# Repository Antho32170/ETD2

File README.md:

# SESAME
Projet ETD18 BALMA

The SESAME project is a DC-DC converter which can be pluged from either side.

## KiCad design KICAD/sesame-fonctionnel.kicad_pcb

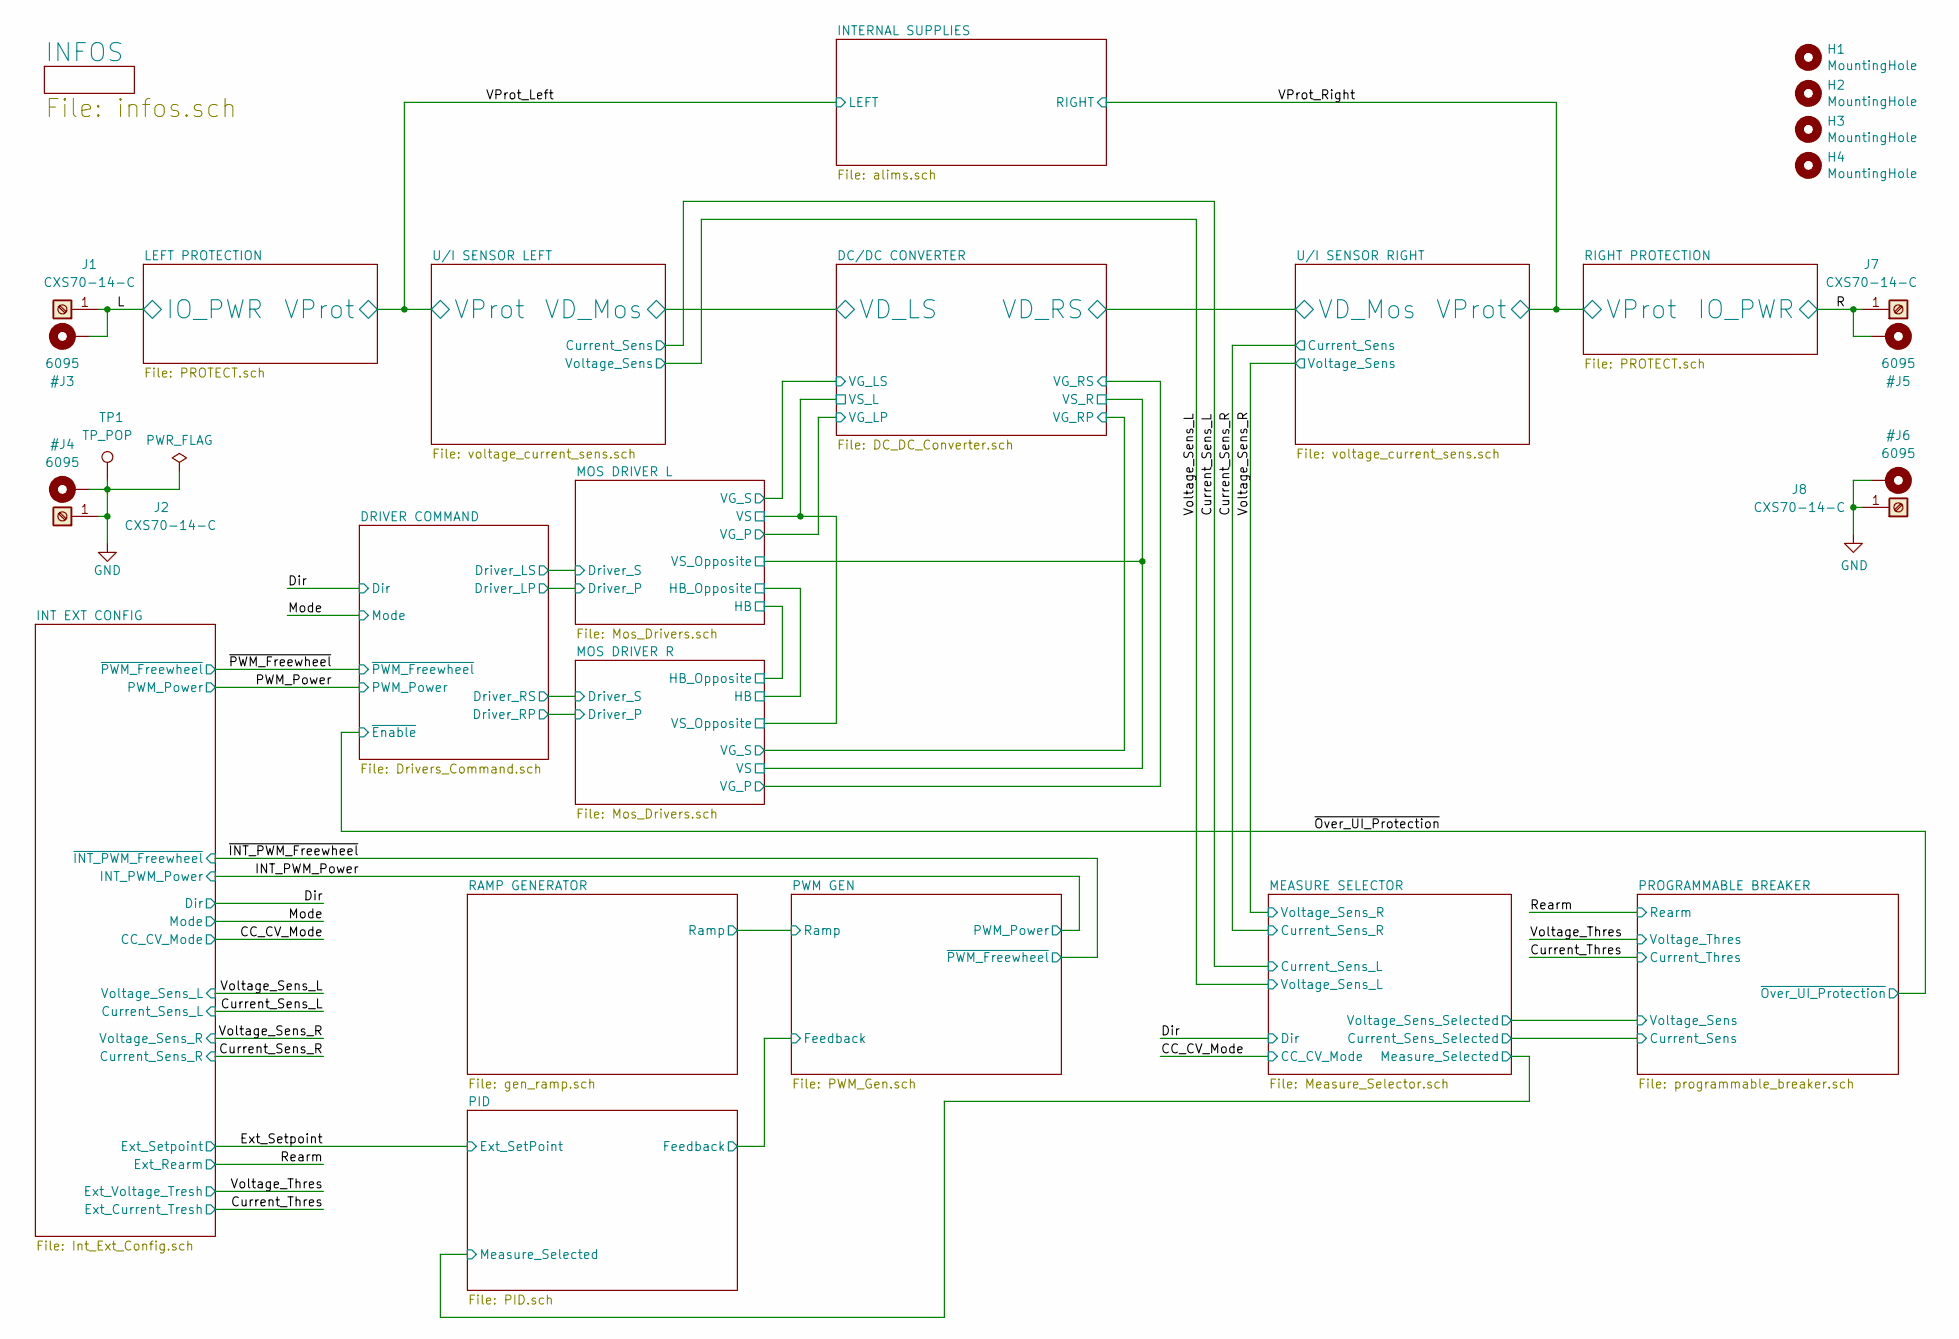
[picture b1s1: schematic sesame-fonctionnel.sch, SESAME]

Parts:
H1, H2, H3, H4: MountingHole; MountingHole_3.2mm_M3
J1, J2, J7, J8: CXS70-14-C
TP1: TP_POP; TestPoint_Loop_D1.80mm_Drill1.0mm_Beaded

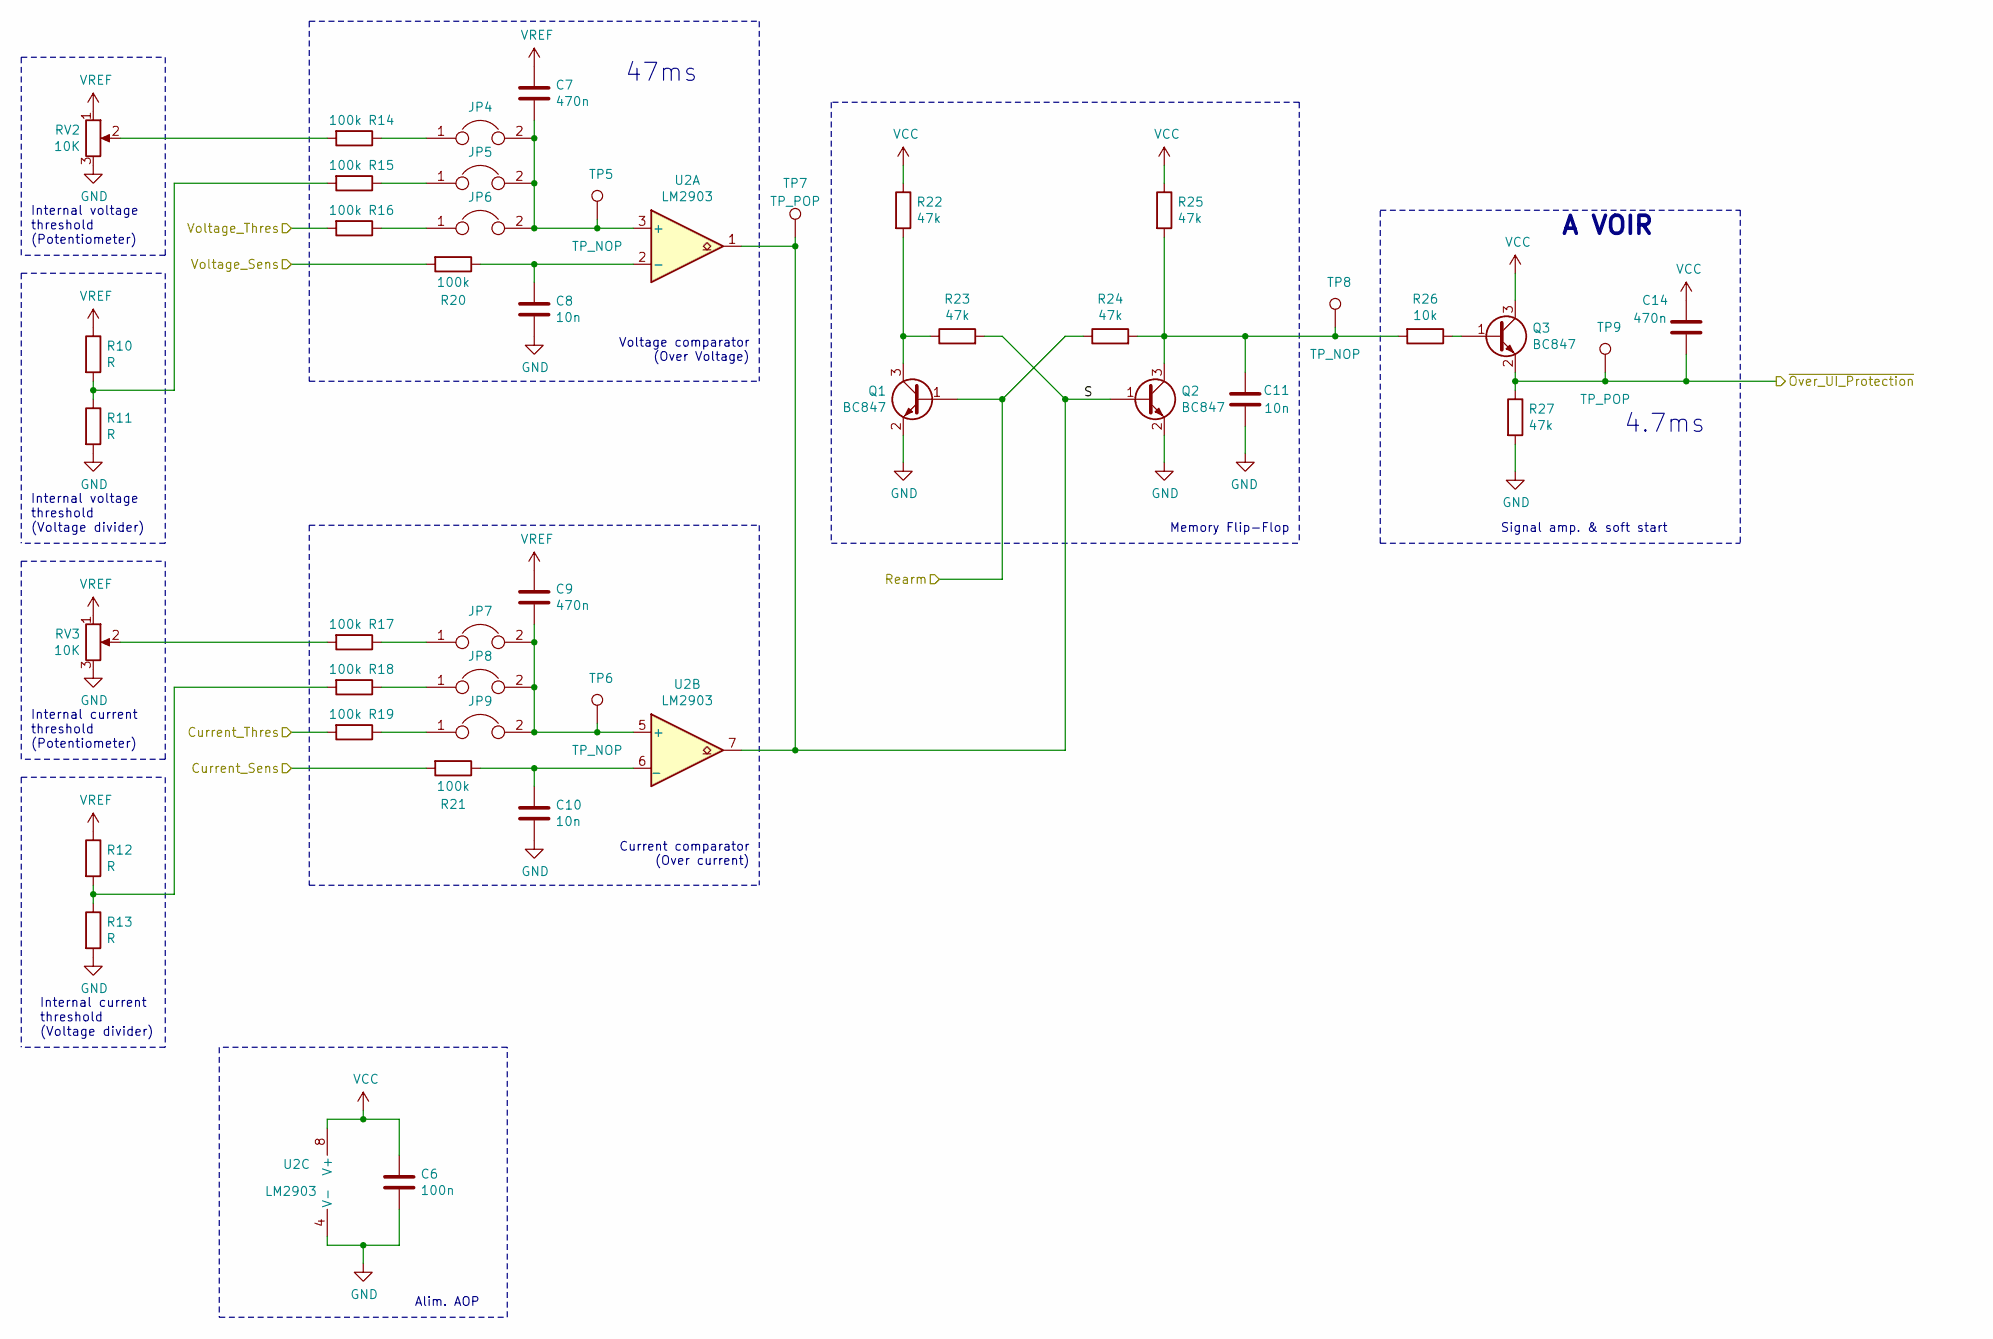
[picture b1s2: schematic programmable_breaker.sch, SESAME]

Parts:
C6: 100n; C_0805_2012Metric_Pad1.18x1.45mm_HandSolder
C7, C9, C14: 470n; C_0805_2012Metric_Pad1.18x1.45mm_HandSolder
C8, C10, C11: 10n; C_0805_2012Metric_Pad1.18x1.45mm_HandSolder
JP4, JP5, JP6, JP7, JP8, JP9: Jumper; PinHeader_1x02_P2.54mm_Vertical
Q1, Q2, Q3: BC847; SOT-23
R10, R11, R12, R13: R; R_0805_2012Metric_Pad1.20x1.40mm_HandSolder
R14, R15, R16, R17, R18, R19, R20, R21: 100k; R_0805_2012Metric_Pad1.20x1.40mm_HandSolder
R22, R23, R24, R25, R27: 47k; R_0805_2012Metric_Pad1.20x1.40mm_HandSolder
R26: 10k; R_0805_2012Metric_Pad1.20x1.40mm_HandSolder
RV2, RV3: 10K; Potentiometer_Bourns_3214W_Vertical
TP5, TP6, TP8: TP_NOP; TestPoint_THTPad_D2.0mm_Drill1.0mm
TP7, TP9: TP_POP; TestPoint_Loop_D1.80mm_Drill1.0mm_Beaded
U2: LM2903; SO-8_5.3x6.2mm_P1.27mm

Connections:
/Current_Thres: R19.2; also elsewhere on the board
/PROGRAMMABLE BREAKER/Current_Sens: R21.2; also elsewhere on the board
/PROGRAMMABLE BREAKER/S: Q2.1 (B), R23.2, TP7.1, U2.1, U2.7
/PROGRAMMABLE BREAKER/Voltage_Sens: R20.2; also elsewhere on the board
/Rearm: Q1.1 (B), R24.1; also elsewhere on the board
/Voltage_Thres: R16.2; also elsewhere on the board
/~Over_UI_Protection: C14.2, Q3.2 (E), R27.1, TP9.1; also elsewhere on the board
unnamed: C7.2, JP4.2, JP5.2, JP6.2, TP5.1, U2.3 (+)
unnamed: C8.1, R20.1, U2.2 (-)
unnamed: C9.2, JP7.2, JP8.2, JP9.2, TP6.1, U2.5 (+)
unnamed: C10.1, R21.1, U2.6 (_)
unnamed: C11.1, Q2.3 (C), R24.2, R25.2, R26.2, TP8.1
unnamed: JP4.1, R14.1
unnamed: JP5.1, R15.1
unnamed: JP6.1, R16.1
unnamed: JP7.1, R17.1
unnamed: JP8.1, R18.1
unnamed: JP9.1, R19.1
unnamed: Q1.3 (C), R22.2, R23.1
unnamed: Q3.1 (B), R26.1
unnamed: R10.2, R11.1, R15.2
unnamed: R12.2, R13.1, R18.2
unnamed: R14.2, RV2.2
unnamed: R17.2, RV3.2
VCC: C6.1, C14.1, Q3.3 (C), R22.1, R25.1, U2.8 (V+); also elsewhere on the board
VREF: C7.1, C9.1, R10.1, R12.1, RV2.1, RV3.1; also elsewhere on the board

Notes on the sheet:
Voltage comparator (Over Voltage)
Memory Flip-Flop
Alim. AOP
Signal amp. & soft start
Internal voltage threshold (Potentiometer)
Internal voltage threshold (Voltage divider)
Current comparator (Over current)
Internal current threshold (Voltage divider)
Internal current threshold (Potentiometer)
4.7ms
47ms
A VOIR

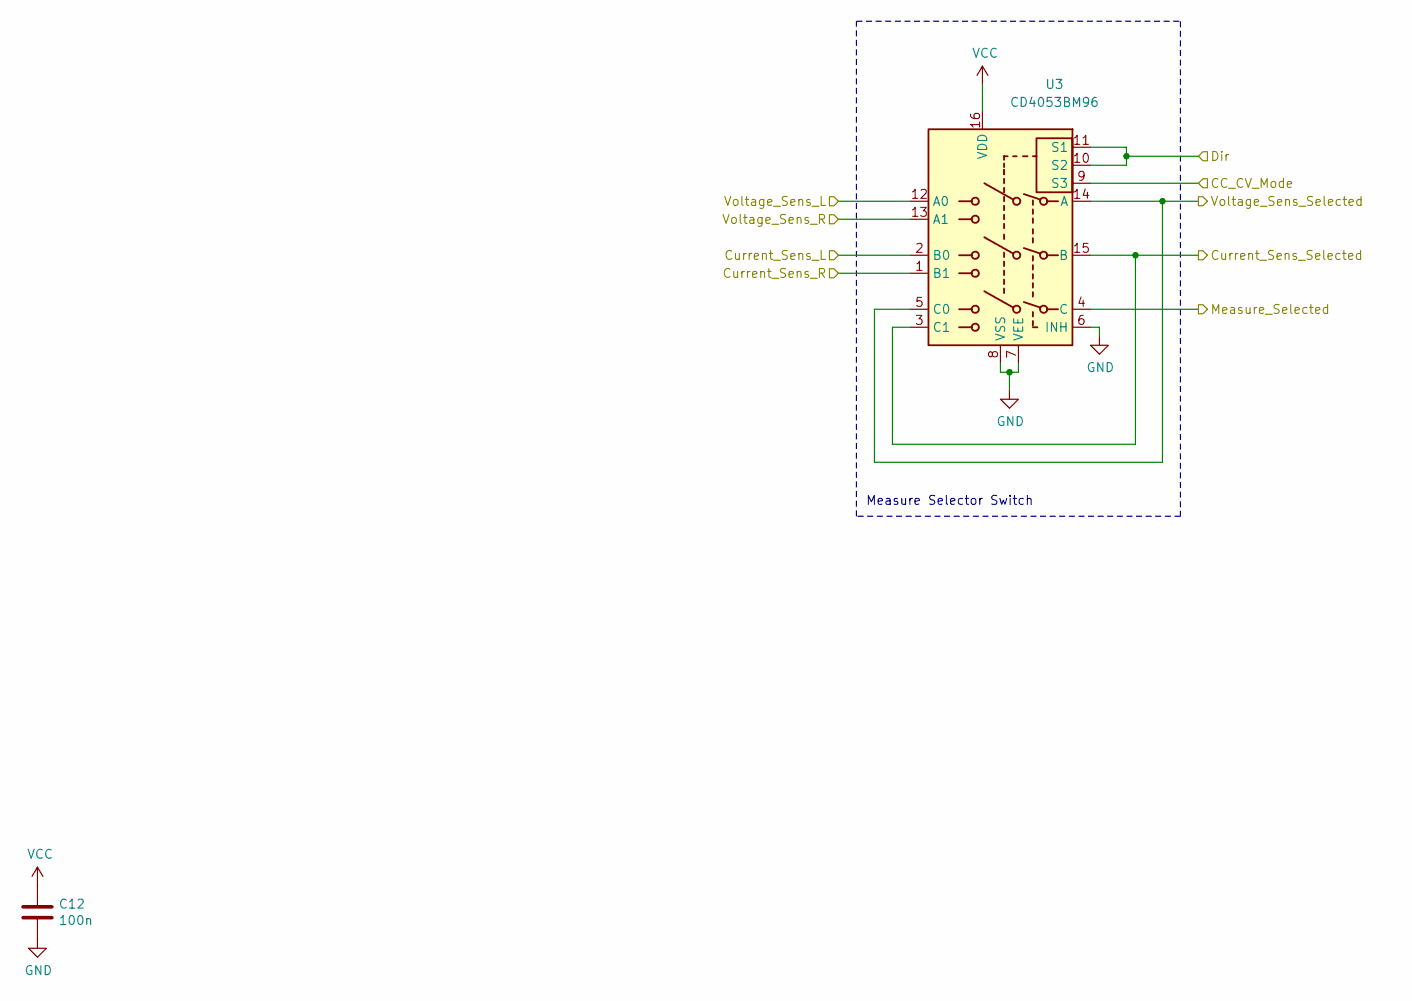
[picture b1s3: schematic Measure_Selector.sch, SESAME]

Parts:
C12: 100n; C_0805_2012Metric_Pad1.18x1.45mm_HandSolder
U3: CD4053BM96; SOIC-16_3.9x9.9mm_P1.27mm

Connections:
/CC_CV_Mode: U3.9 (S3); also elsewhere on the board
/Current_Sens_L: U3.2 (B0); also elsewhere on the board
/Current_Sens_R: U3.1 (B1); also elsewhere on the board
/Dir: U3.10 (S2), U3.11 (S1); also elsewhere on the board
/MEASURE SELECTOR/Measure_Selected: U3.4 (C); also elsewhere on the board
/PROGRAMMABLE BREAKER/Current_Sens: U3.3 (C1), U3.15 (B); also elsewhere on the board
/PROGRAMMABLE BREAKER/Voltage_Sens: U3.5 (C0), U3.14 (A); also elsewhere on the board
/Voltage_Sens_L: U3.12 (A0); also elsewhere on the board
/Voltage_Sens_R: U3.13 (A1); also elsewhere on the board
VCC: C12.1, U3.16 (VDD); also elsewhere on the board

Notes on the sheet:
Measure Selector Switch

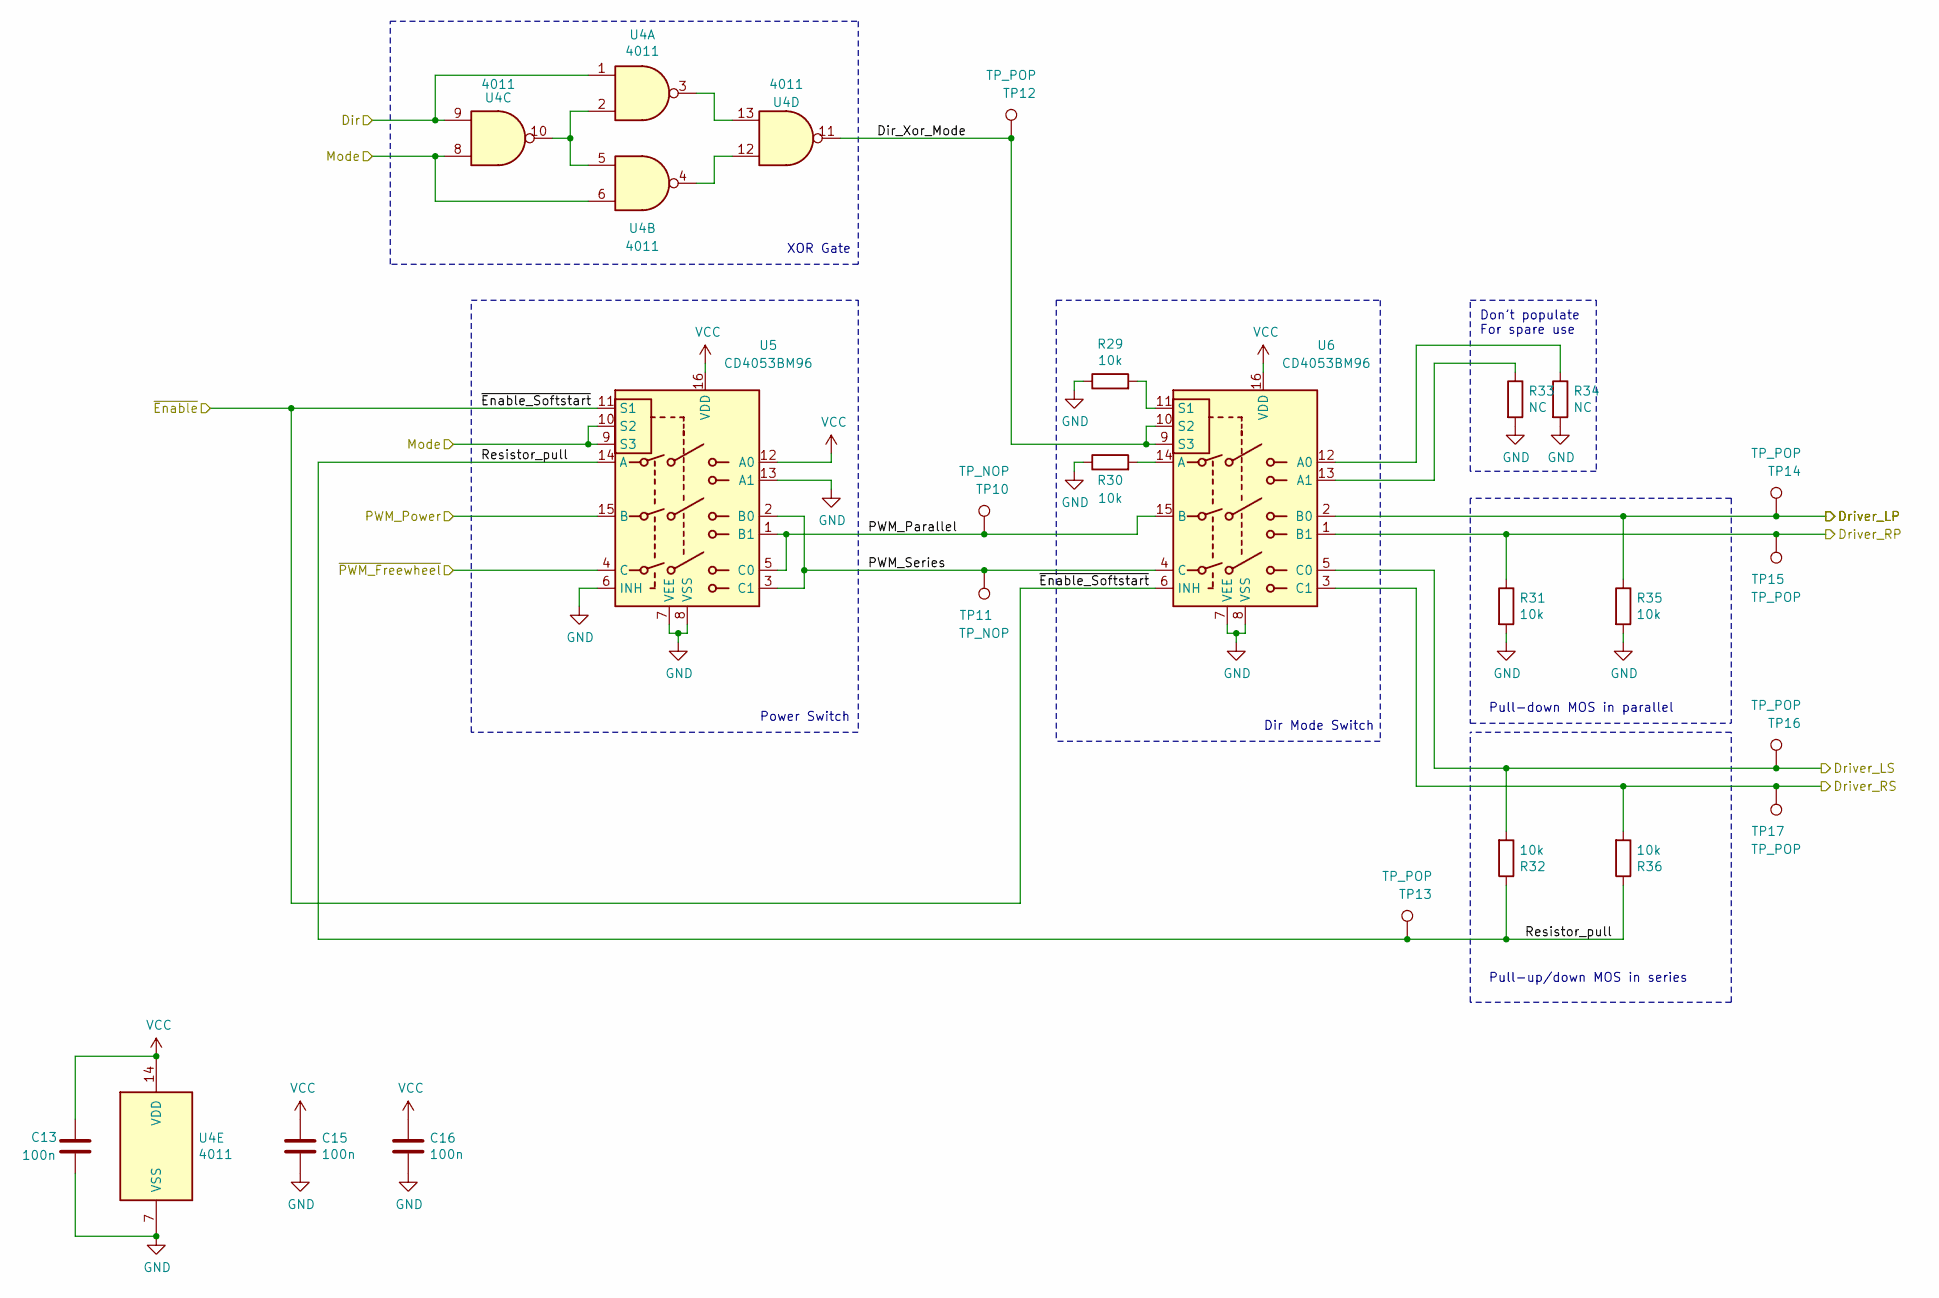
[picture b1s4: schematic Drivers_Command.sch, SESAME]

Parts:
C13, C15, C16: 100n; C_0805_2012Metric_Pad1.18x1.45mm_HandSolder
R29, R30, R31, R32, R35, R36: 10k; R_0805_2012Metric_Pad1.20x1.40mm_HandSolder
R33, R34: NC; R_0805_2012Metric_Pad1.20x1.40mm_HandSolder
TP10, TP11: TP_NOP; TestPoint_THTPad_D2.0mm_Drill1.0mm
TP12, TP13, TP14, TP15, TP16, TP17: TP_POP; TestPoint_Loop_D1.80mm_Drill1.0mm_Beaded
U4: 4011; SOIC-14_3.9x8.7mm_P1.27mm
U5, U6: CD4053BM96; SOIC-16_3.9x9.9mm_P1.27mm

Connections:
/DRIVER COMMAND/Dir_Xor_Mode: TP12.1, U4.11, U6.9 (S3), U6.10 (S2)
/DRIVER COMMAND/Driver_LP: R35.1, TP14.1, U6.2 (B0); also elsewhere on the board
/DRIVER COMMAND/Driver_LS: R32.2, TP16.1, U6.5 (C0); also elsewhere on the board
/DRIVER COMMAND/Driver_RS: R36.2, TP17.1, U6.3 (C1); also elsewhere on the board
/DRIVER COMMAND/PWM_Parallel: TP10.1, U5.1 (B1), U5.5 (C0), U6.15 (B)
/DRIVER COMMAND/PWM_Series: TP11.1, U5.2 (B0), U5.3 (C1), U6.4 (C)
/DRIVER COMMAND/Resistor_pull: R32.1, R36.1, TP13.1, U5.14 (A)
/Dir: U4.1, U4.9; also elsewhere on the board
/MOS DRIVER R/Driver_P: R31.1, TP15.1, U6.1 (B1); also elsewhere on the board
/Mode: U4.6, U4.8, U5.9 (S3), U5.10 (S2); also elsewhere on the board
/PWM_Power: U5.15 (B); also elsewhere on the board
/~Over_UI_Protection: U5.11 (S1), U6.6 (INH); also elsewhere on the board
/~PWM_Freewheel: U5.4 (C); also elsewhere on the board
unnamed: R29.2, U6.11 (S1)
unnamed: R30.2, U6.14 (A)
unnamed: R33.1, U6.13 (A1)
unnamed: R34.1, U6.12 (A0)
unnamed: U4.2, U4.5, U4.10
unnamed: U4.4, U4.12
unnamed: U4.3, U4.13
VCC: C13.1, C15.1, C16.1, U4.14 (VDD), U5.12 (A0), U5.16 (VDD), U6.16 (VDD); also elsewhere on the board

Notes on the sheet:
Pull-down MOS in parallel
XOR Gate
Don’t populate For spare use
Pull-up/down MOS in series
Power Switch
Dir Mode Switch

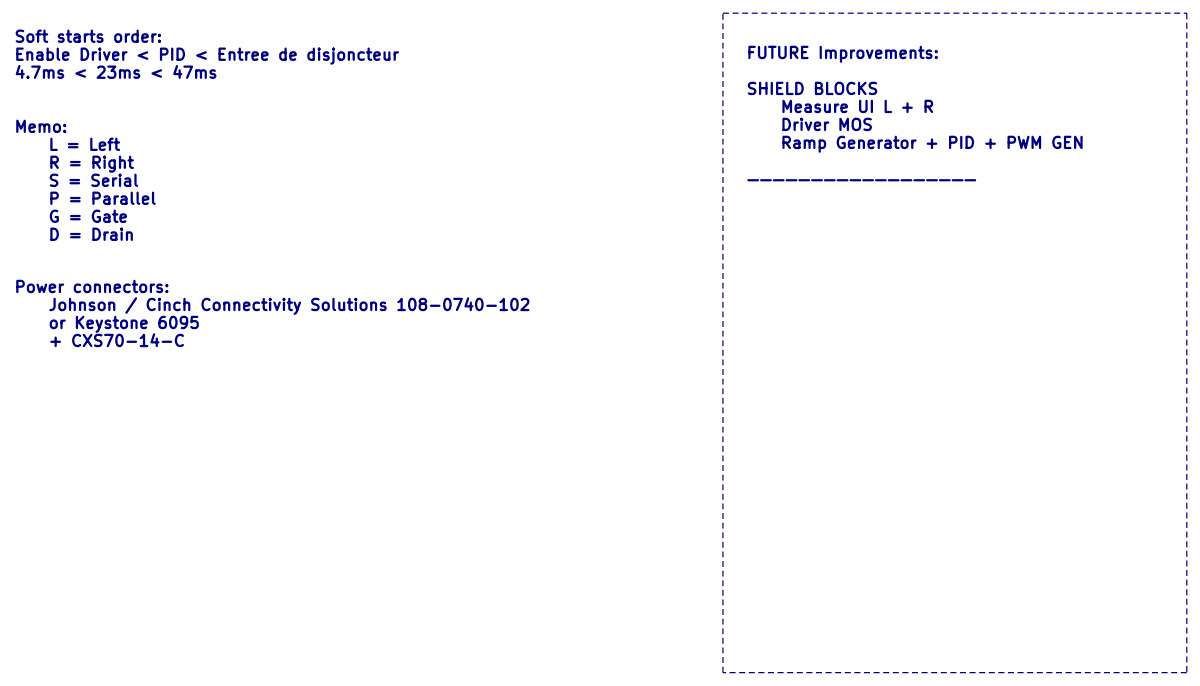
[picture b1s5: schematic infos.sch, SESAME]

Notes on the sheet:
Soft starts order: Enable Driver < PID < Entree de disjoncteur 4.7ms < 23ms < 47ms
FUTURE Improvements: SHIELD BLOCKS Measure UI L + R Driver MOS Ramp Generator + PID + PWM GEN ——————————————————
Memo: L = Left R = Right S = Serial P = Parallel G = Gate D = Drain
Power connectors: Johnson / Cinch Connectivity Solutions 108-0740-102 or Keystone 6095 + CXS70-14-C

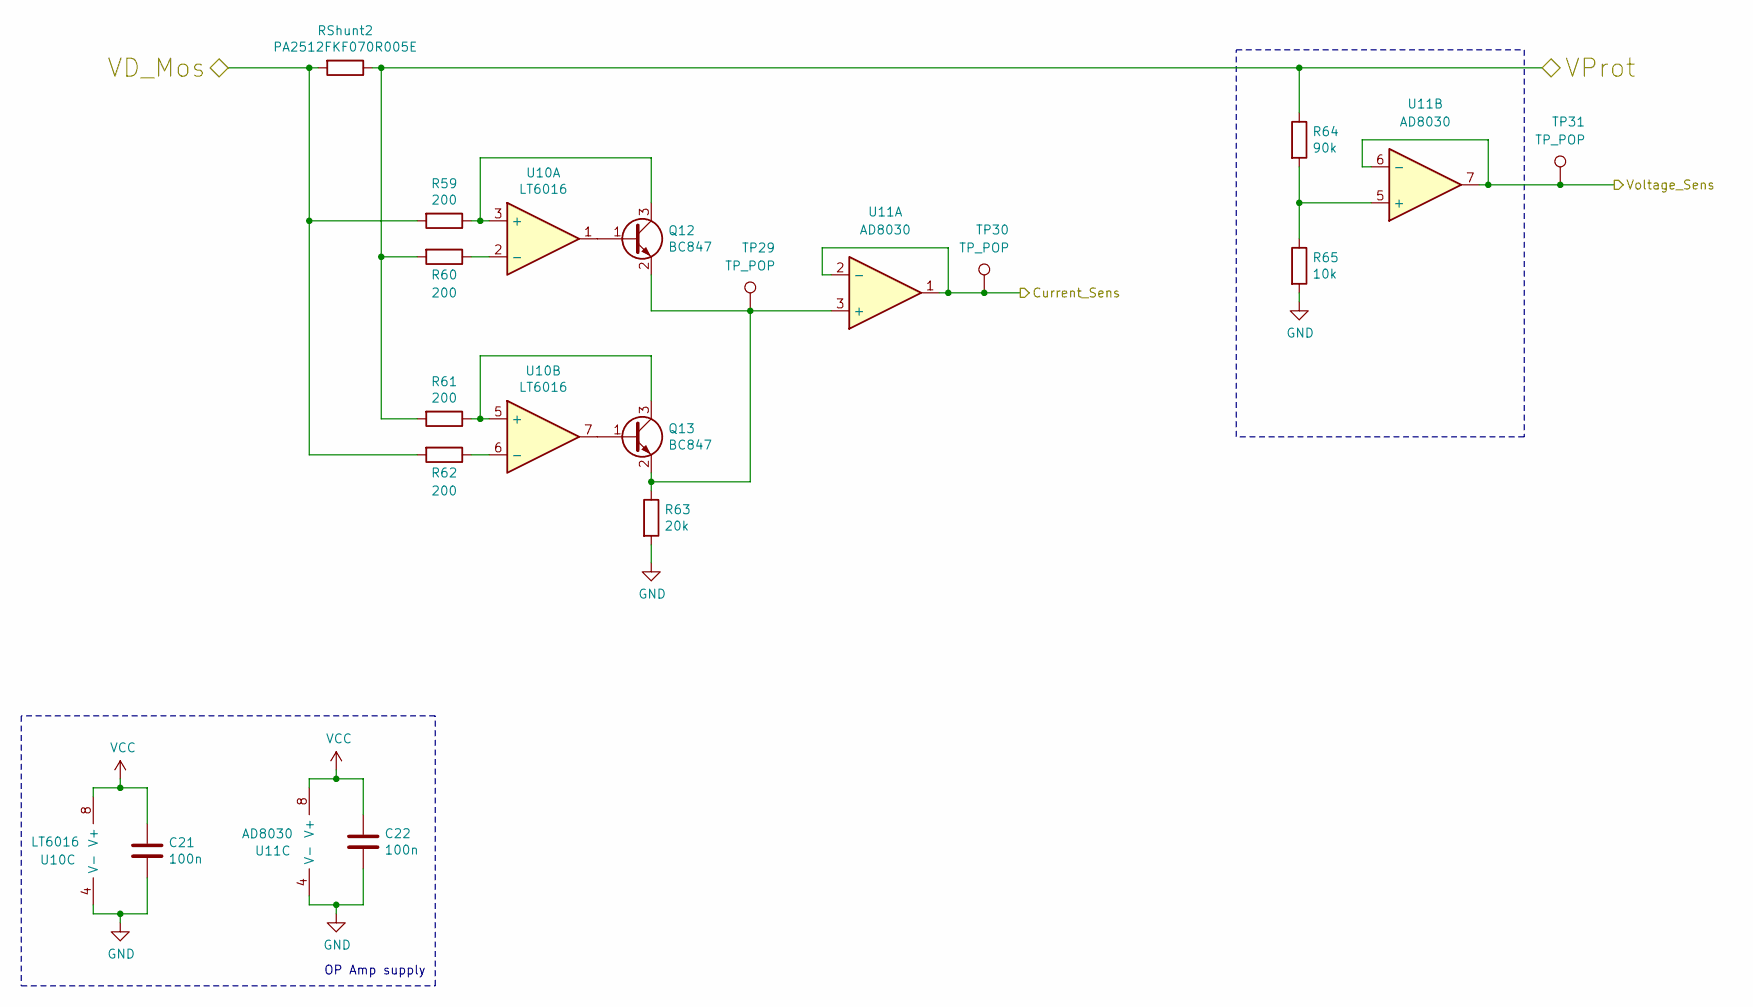
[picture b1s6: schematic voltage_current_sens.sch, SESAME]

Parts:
C19, C20: 100n; C_0805_2012Metric_Pad1.18x1.45mm_HandSolder
Q4, Q5: BC847; SOT-23
R48: 20k; R_0805_2012Metric_Pad1.20x1.40mm_HandSolder
R49: 90k; R_0805_2012Metric_Pad1.20x1.40mm_HandSolder
R50: 10k; R_0805_2012Metric_Pad1.20x1.40mm_HandSolder
R59, R60, R61, R62: 200; R_0805_2012Metric_Pad1.20x1.40mm_HandSolder
RShunt2: PA2512FKF070R005E; R_2512_6332Metric_Pad1.52x3.35mm_HandSolder
TP20, TP21, TP22: TP_POP; TestPoint_Loop_D1.80mm_Drill1.0mm_Beaded
U8: LT6016; MSOP-8_3x3mm_P0.65mm
U9: AD8030; SO-8_5.3x6.2mm_P1.27mm

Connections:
/Current_Sens_L: TP21.1, U9.1, U9.2 (-); also elsewhere on the board
/U/I SENSOR RIGHT/VD_Mos: R59.2, R62.2, RShunt2.2; also elsewhere on the board
/Voltage_Sens_L: TP22.1, U9.6 (-), U9.7; also elsewhere on the board
unnamed: Q4.1 (B), U8.1
unnamed: Q4.2 (E), Q5.2 (E), R48.1, TP20.1, U9.3 (+)
unnamed: Q5.1 (B), U8.7
unnamed: R49.2, R50.1, U9.5 (+)
VCC: C19.1, C20.1, U8.8 (V+), U9.8 (V+); also elsewhere on the board

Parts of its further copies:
C21, C22: 100n; C_0805_2012Metric_Pad1.18x1.45mm_HandSolder
Q12, Q13: BC847; SOT-23
R44, R45, R46, R47: 200; R_0805_2012Metric_Pad1.20x1.40mm_HandSolder
R63: 20k; R_0805_2012Metric_Pad1.20x1.40mm_HandSolder
R64: 90k; R_0805_2012Metric_Pad1.20x1.40mm_HandSolder
R65: 10k; R_0805_2012Metric_Pad1.20x1.40mm_HandSolder
RShunt1: PA2512FKF070R005E; R_2512_6332Metric_Pad1.52x3.35mm_HandSolder
TP29, TP30, TP31: TP_POP; TestPoint_Loop_D1.80mm_Drill1.0mm_Beaded
U10: LT6016; MSOP-8_3x3mm_P0.65mm
U11: AD8030; SO-8_5.3x6.2mm_P1.27mm

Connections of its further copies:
/Current_Sens_R: TP30.1, U11.1, U11.2 (-); also elsewhere on the board
/DC/DC CONVERTER/VD_LS: R44.2, R47.2, RShunt1.2; also elsewhere on the board
/Voltage_Sens_R: TP31.1, U11.6 (-), U11.7; also elsewhere on the board
unnamed: Q12.1 (B), U10.1
unnamed: Q12.2 (E), Q13.2 (E), R63.1, TP29.1, U11.3 (+)
unnamed: Q13.1 (B), U10.7
unnamed: R64.2, R65.1, U11.5 (+)
VCC: C21.1, C22.1, U10.8 (V+), U11.8 (V+); also elsewhere on the board

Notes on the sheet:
OP Amp supply

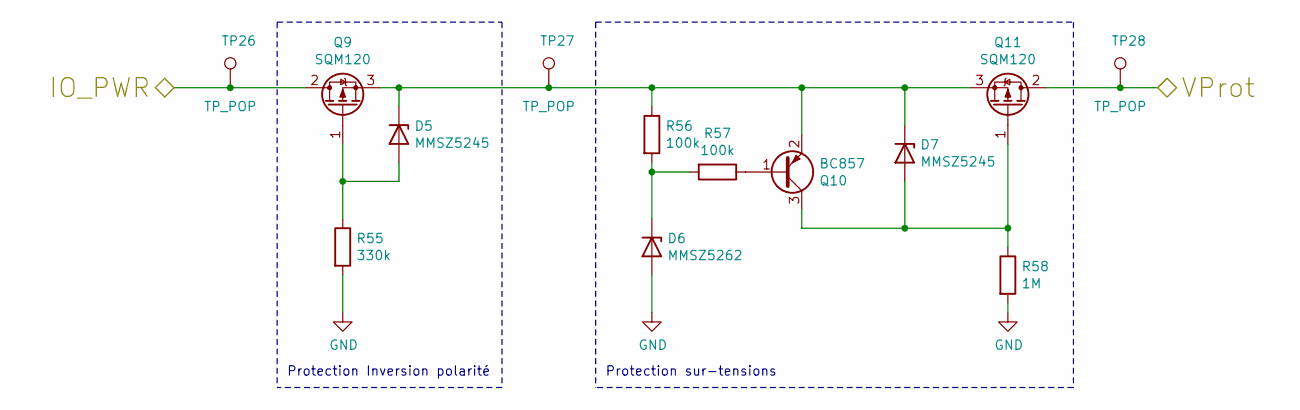
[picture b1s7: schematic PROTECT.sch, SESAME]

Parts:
D5, D7: MMSZ5245; D_SOD-123
D6: MMSZ5262; D_SOD-123
Q9, Q11: SQM120; TO-263-2
Q10: BC857; SOT-23
R55: 330k; R_0805_2012Metric_Pad1.20x1.40mm_HandSolder
R56, R57: 100k; R_0805_2012Metric_Pad1.20x1.40mm_HandSolder
R58: 1M; R_0805_2012Metric_Pad1.20x1.40mm_HandSolder
TP26, TP27, TP28: TP_POP; TestPoint_Loop_D1.80mm_Drill1.0mm_Beaded

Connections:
unnamed: D5.1 (K), D7.1 (K), Q9.3 (S), Q10.2 (E), Q11.3 (S), R56.1, TP27.1
unnamed: D5.2 (A), Q9.1 (G), R55.1
unnamed: D6.1 (K), R56.2, R57.2
unnamed: D7.2 (A), Q10.3 (C), Q11.1 (G), R58.1
unnamed: Q10.1 (B), R57.1

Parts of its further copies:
D2, D4: MMSZ5245; D_SOD-123
D3: MMSZ5262; D_SOD-123
Q6, Q8: SQM120; TO-263-2
Q7: BC857; SOT-23
R51: 330k; R_0805_2012Metric_Pad1.20x1.40mm_HandSolder
R52, R53: 100k; R_0805_2012Metric_Pad1.20x1.40mm_HandSolder
R54: 1M; R_0805_2012Metric_Pad1.20x1.40mm_HandSolder
TP23, TP24, TP25: TP_POP; TestPoint_Loop_D1.80mm_Drill1.0mm_Beaded

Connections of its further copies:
unnamed: D2.1 (K), D4.1 (K), Q6.3 (S), Q7.2 (E), Q8.3 (S), R52.1, TP24.1
unnamed: D2.2 (A), Q6.1 (G), R51.1
unnamed: D3.1 (K), R52.2, R53.2
unnamed: D4.2 (A), Q7.3 (C), Q8.1 (G), R54.1
unnamed: Q7.1 (B), R53.1

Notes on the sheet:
Protection sur-tensions
Protection Inversion polarité

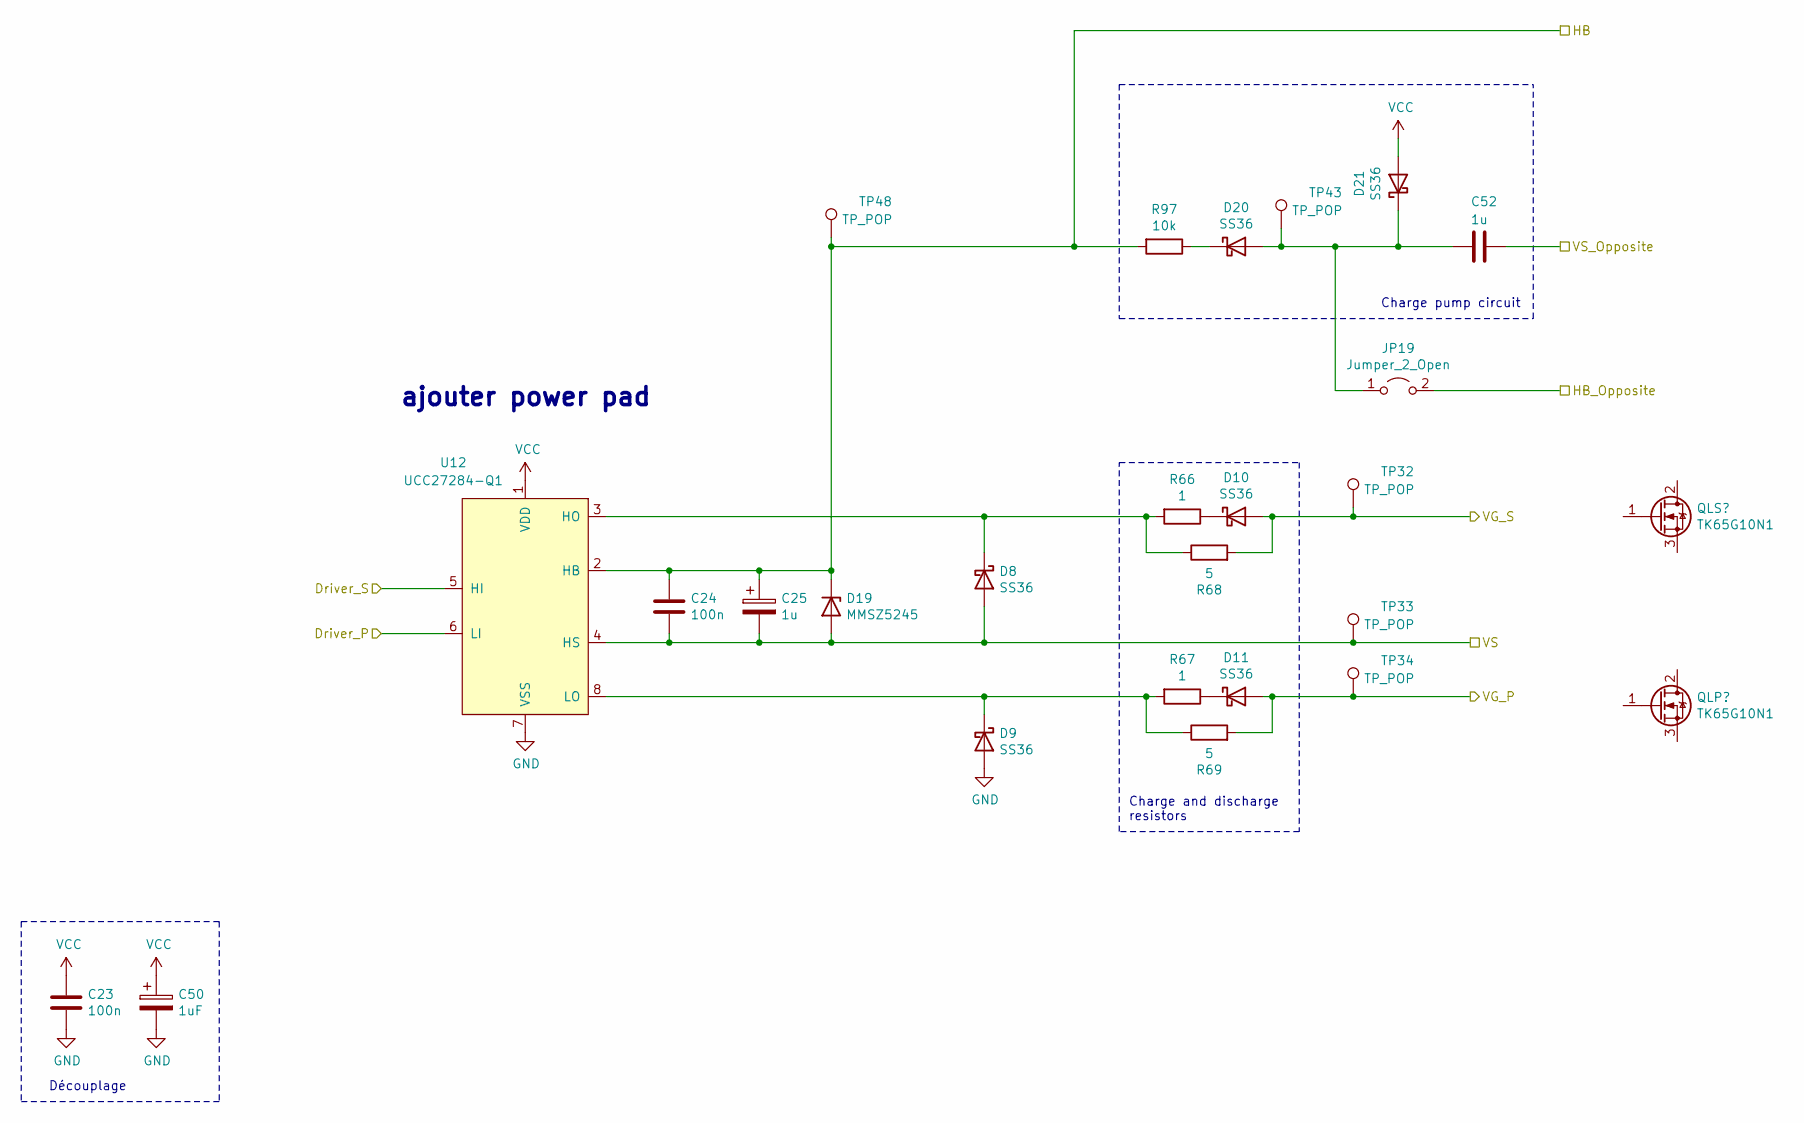
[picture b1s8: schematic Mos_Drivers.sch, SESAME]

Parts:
C23, C24: 100n; C_0805_2012Metric_Pad1.18x1.45mm_HandSolder
C25, C52: 1u; C_0805_2012Metric_Pad1.18x1.45mm_HandSolder
C50: 1uF; C_0805_2012Metric_Pad1.18x1.45mm_HandSolder
D8, D9, D10, D11, D20, D21: SS36; D_SMA_Handsoldering
D19: MMSZ5245; D_SOD-123
JP19: Jumper_2_Open; SolderJumper-2_P1.3mm_Open_TrianglePad1.0x1.5mm
R66, R67: 1; R_0805_2012Metric_Pad1.20x1.40mm_HandSolder
R68, R69: 5; R_0805_2012Metric_Pad1.20x1.40mm_HandSolder
R97: 10k; R_0805_2012Metric_Pad1.20x1.40mm_HandSolder
TP32, TP33, TP34, TP43, TP48: TP_POP; TestPoint_Loop_D1.80mm_Drill1.0mm_Beaded
U12: UCC27284-Q1; SOIC-8_3.9x4.9mm_P1.27mm

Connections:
/DC/DC CONVERTER/VG_LP: D11.2 (A), R69.2, TP34.1; also elsewhere on the board
/DC/DC CONVERTER/VG_LS: D10.2 (A), R68.2, TP32.1; also elsewhere on the board
/DRIVER COMMAND/Driver_LP: U12.6 (LI); also elsewhere on the board
/DRIVER COMMAND/Driver_LS: U12.5 (HI); also elsewhere on the board
/MOS DRIVER L/HB: C24.1, C25.1, D19.1 (K), R97.2, TP48.1, U12.2 (HB); also elsewhere on the board
/MOS DRIVER L/VS: C24.2, C25.2, D8.2 (A), D19.2 (A), TP33.1, U12.4 (HS); also elsewhere on the board
/MOS DRIVER R/HB: JP19.2 (B); also elsewhere on the board
/MOS DRIVER R/VS: C52.1; also elsewhere on the board
unnamed: C52.2, D20.2 (A), D21.1 (K), JP19.1 (A), TP43.1
unnamed: D8.1 (K), R66.2, R68.1, U12.3 (HO)
unnamed: D9.1 (K), R67.2, R69.1, U12.8 (LO)
unnamed: D10.1 (K), R66.1
unnamed: D11.1 (K), R67.1
unnamed: D20.1 (K), R97.1
VCC: C23.1, C50.1, D21.2 (A), U12.1 (VDD); also elsewhere on the board

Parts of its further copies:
C33, C34: 100n; C_0805_2012Metric_Pad1.18x1.45mm_HandSolder
C35, C53: 1u; C_0805_2012Metric_Pad1.18x1.45mm_HandSolder
C51: 1uF; C_0805_2012Metric_Pad1.18x1.45mm_HandSolder
D15, D16, D17, D18, D23, D24: SS36; D_SMA_Handsoldering
D22: MMSZ5245; D_SOD-123
JP20: Jumper_2_Open; SolderJumper-2_P1.3mm_Open_TrianglePad1.0x1.5mm
R85, R86: 1; R_0805_2012Metric_Pad1.20x1.40mm_HandSolder
R87, R88: 5; R_0805_2012Metric_Pad1.20x1.40mm_HandSolder
R98: 10k; R_0805_2012Metric_Pad1.20x1.40mm_HandSolder
TP44, TP45, TP46, TP47, TP49: TP_POP; TestPoint_Loop_D1.80mm_Drill1.0mm_Beaded
U17: UCC27284-Q1; SOIC-8_3.9x4.9mm_P1.27mm

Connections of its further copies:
/DC/DC CONVERTER/VG_RP: D17.2 (A), R87.2, TP45.1; also elsewhere on the board
/DRIVER COMMAND/Driver_RS: U17.5 (HI); also elsewhere on the board
/MOS DRIVER L/HB: JP20.2 (B); also elsewhere on the board
/MOS DRIVER L/VS: C53.1; also elsewhere on the board
/MOS DRIVER R/Driver_P: U17.6 (LI); also elsewhere on the board
/MOS DRIVER R/HB: C34.1, C35.1, D22.1 (K), R98.2, TP49.1, U17.2 (HB); also elsewhere on the board
/MOS DRIVER R/VG_P: D18.2 (A), R88.2, TP47.1; also elsewhere on the board
/MOS DRIVER R/VS: C34.2, C35.2, D15.2 (A), D22.2 (A), TP46.1, U17.4 (HS); also elsewhere on the board
unnamed: C53.2, D23.2 (A), D24.1 (K), JP20.1 (A), TP44.1
unnamed: D15.1 (K), R85.2, R87.1, U17.3 (HO)
unnamed: D16.1 (K), R86.2, R88.1, U17.8 (LO)
unnamed: D17.1 (K), R85.1
unnamed: D18.1 (K), R86.1
unnamed: D23.1 (K), R98.1
VCC: C33.1, C51.1, D24.2 (A), U17.1 (VDD); also elsewhere on the board

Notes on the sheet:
Découplage
ajouter power pad
Charge pump circuit
Charge and discharge resistors

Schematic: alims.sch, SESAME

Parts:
C27: 100n; C_0805_2012Metric_Pad1.18x1.45mm_HandSolder
C28, C29, C31: C; C_0805_2012Metric_Pad1.18x1.45mm_HandSolder
C30: 10u; C_1206_3216Metric_Pad1.42x1.75mm_HandSolder
C32: CP; C_Elec_4x5.8
D12, D13, D14: SS36; D_SMA_Handsoldering
L1: L_Core_Ferrite_Coupled_2_Parts; WE-DD_1260_128012
R28: 14k; R_0805_2012Metric_Pad1.20x1.40mm_HandSolder
R79: 84.5; R_0805_2012Metric_Pad1.20x1.40mm_HandSolder
R80: R; R_0805_2012Metric_Pad1.20x1.40mm_HandSolder
R81: 1M; R_0805_2012Metric_Pad1.20x1.40mm_HandSolder
R82: 296k; R_0805_2012Metric_Pad1.20x1.40mm_HandSolder
R83: 200; R_0805_2012Metric_Pad1.20x1.40mm_HandSolder
R84: 10k; R_0805_2012Metric_Pad1.20x1.40mm_HandSolder
TP39, TP40, TP42: TP_POP; TestPoint_Loop_D1.80mm_Drill1.0mm_Beaded
TP41: TP_NOP; TestPoint_THTPad_D2.0mm_Drill1.0mm
U15: LT8365; MSE-16-1EP_3x4mm_P0.5mm_EP1.65x2.85mm_ThermalVias
U16: TL431DBZ; SOT-23

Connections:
/INTERNAL SUPPLIES/VIN: D12.1 (K), D13.1 (K), L1.1 (2), TP39.1, U15.1 (EN/UVLO), U15.3 (VIN)
unnamed: C28.1, U15.11 (SS)
unnamed: C29.1, R80.2
unnamed: C30.1, D14.2 (A), L1.3, TP41.1
unnamed: C30.2, L1.4 (3), TP40.1, U15.14 (SW2), U15.16 (SW1)
unnamed: C31.1, U15.5 (INTVCC)
unnamed: R28.2, R84.1, U16.2 (REF)
unnamed: R79.1, U15.10 (RT)
unnamed: R80.1, U15.8 (VC)
unnamed: R81.2, R82.1, U15.9 (FBX)
VCC: C32.1, D14.1 (K), R81.1, R83.1, TP42.1, U15.7 (BIAS); also elsewhere on the board
VREF: C27.1, R28.1, R83.2, U16.1 (K); also elsewhere on the board

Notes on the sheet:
RT = 432k -> 100 kHz RT = 143k -> 300 kHz RT = 84.5k -> 500 kHz
VCC = 7V VREF = 6V
